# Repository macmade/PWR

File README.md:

PWR
===

About
-----

+5 volt power supply for breadboards using a 12 volt DC wall adapter or a 9 volt battery.

### Software

Schemas and PCB layouts are created with KiCad:  
http://www.kicad-pcb.org

#### Footprints Library

This project requires the [XS-Labs KiCad Library](https://github.com/macmade/XS-KiCad-Library) to be installed in KiCad.

### Board

Here's what the board looks like:

Bill Of Materials
-----------------

| Manufacturer            | Part No.             | Details                                                                  | Quantity |
|-------------------------|----------------------|--------------------------------------------------------------------------|----------|
| CUI Devices             | [PJ-102AH]           | DC Power Jack                                                            | 1        |
| Keystone Electronics    | [1291]               | 9V Battery Snap Holder                                                   | 1        |
| ON Semiconductor        | [1N4001G]            | Rectifier 50V 1A Standard                                                | 2        |
| Texas Instruments       | [LM7805CT/NOPB]      | Linear Voltage Regulator 5V                                              | 1        |
| Vishay                  | [MAL214250101E3]     | Aluminium Electrolytic Capacitor - Radial Leaded 100uF 35V 20%           | 1        |
| Vishay                  | [MAL214258109E3]     | Aluminium Electrolytic Capacitor - Radial Leaded 10uF 63V 20%            | 1        |
| Murata                  | [RCER71H334K1K1H03B] | Multilayer Ceramic Capacitor - Radial Leaded 0.33uF 50V 10%              | 1        |
| Murata                  | [RCER71H104K0K1H03B] | Multilayer Ceramic Capacitor - Radial Leaded 0.1uF 50V 10%               | 1        |
| VCC                     | [4302H1-12V]         | Standard LEDs - Red - 12V                                                | 1        |
| VCC                     | [4302H3-12V]         | Standard LEDs - Amber - 12V                                              | 1        |
| VCC                     | [4302H5-12V]         | Standard LEDs - Green - 12V                                              | 1        |
| Vishay                  | [CCF071K00JKE36]     | Metal Film Resistor - Through Hole 1/4watt 1Kohms 5%                     | 1        |
| Vishay                  | [CCF07390RJKE36]     | Metal Film Resistor - Through Hole 1/4watt 390ohms 5%                    | 2        |
| NKK Switches            | [M2012SA1W03]        | Toggle Switch ON-ON PC SPDT                                              | 1        |
| Wurth Elektronik        | [691214110002]       | Fixed Terminal Block WR-TBL 300VAC 10A 2P Horizontal                     | 1        |

[PJ-102AH]: https://www.mouser.ch/ProductDetail/490-PJ-102AH
[1291]: https://www.mouser.ch/ProductDetail/534-1291
[1N4001G]: https://www.mouser.ch/ProductDetail/863-1N4001G
[LM7805CT/NOPB]: https://www.mouser.ch/ProductDetail/926-LM7805CT-NOPB
[MAL214250101E3]: https://www.mouser.ch/ProductDetail/594-MAL214250101E3
[MAL214258109E3]: https://www.mouser.ch/ProductDetail/594-MAL214258109E3
[RCER71H334K1K1H03B]: https://www.mouser.ch/ProductDetail/81-RCER71H334K1K1H3B
[RCER71H104K0K1H03B]: https://www.mouser.ch/ProductDetail/81-RCER71H104K0K1H3B
[4302H1-12V]: https://www.mouser.ch/ProductDetail/606-4302H1-12V
[4302H3-12V]: https://www.mouser.ch/ProductDetail/606-4302H3-12V
[4302H5-12V]: https://www.mouser.ch/ProductDetail/606-4302H5-12V
[CCF071K00JKE36]: https://www.mouser.ch/ProductDetail/71-CCF071K00JKE36
[CCF07390RJKE36]: https://www.mouser.ch/ProductDetail/71-CCF07390RJKE36
[M2012SA1W03]: https://www.mouser.ch/ProductDetail/633-M2012A03
[691214110002]: https://www.mouser.ch/ProductDetail/710-691214110002

License
-------

All project files are released under the terms of the CERN Open Hardware License - CERN OHL v.1.2.

Repository Infos
----------------

    Owner:          Jean-David Gadina - XS-Labs
    Web:            www.xs-labs.com
    Blog:           www.noxeos.com
    Twitter:        @macmade
    GitHub:         github.com/macmade
    LinkedIn:       ch.linkedin.com/in/macmade/
    StackOverflow:  stackoverflow.com/users/182676/macmade

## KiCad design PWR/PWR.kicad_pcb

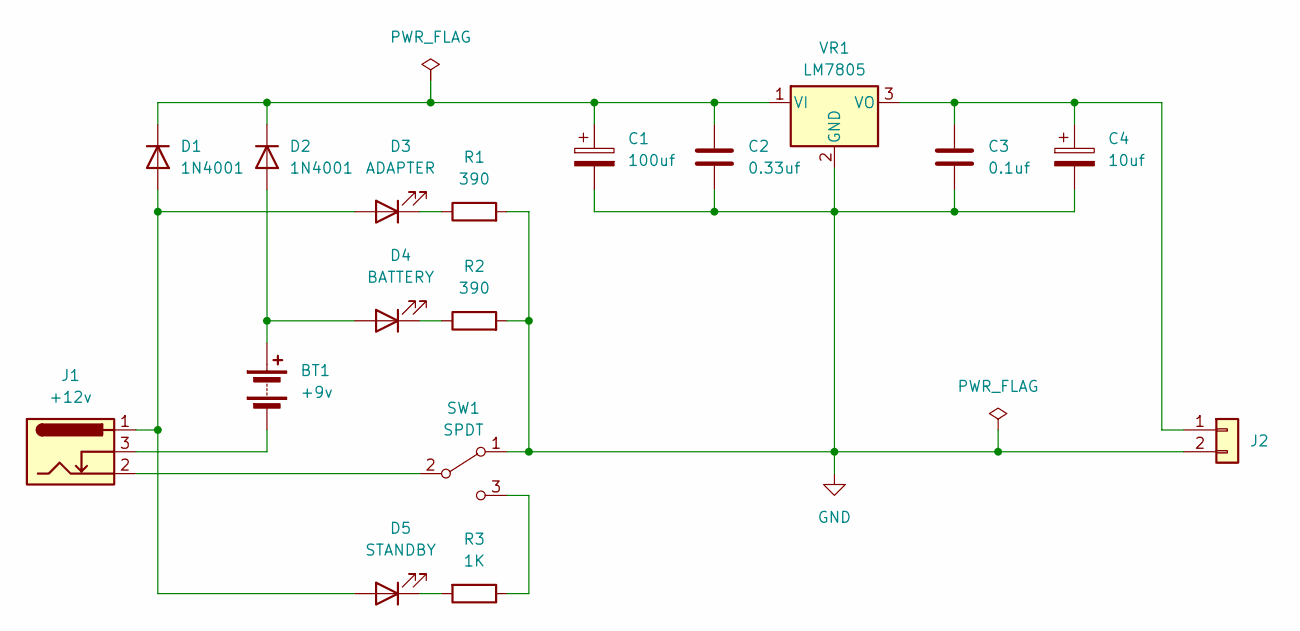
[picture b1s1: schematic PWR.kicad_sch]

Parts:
BT1: +9v; Battery-Keystone-1291-9v-Holder
C1: 100uf; Capacitor-Vishay-142-RHS-6.3x11x2.5mm
C2: 0.33uf; Capacitor-Murata-RCE-K-5mm.step
C3: 0.1uf; Capacitor-Murata-RCE-K-5mm.step
C4: 10uf; Capacitor-Vishay-142-RHS-5x11x2mm
D1, D2: 1N4001; Diode-DO-41
D3: ADAPTER; LED-T1-34-5mm-tabs
D4: BATTERY; LED-T1-34-5mm-tabs
D5: STANDBY; LED-T1-34-5mm-tabs
J1: +12v; Plug-DC-Barrel-Jack-2.1mm-CUI-PJ-102AH
J2: Connector-Wurth-Terminal-Block-2P-3.5mm-691214110002
R1, R2: 390; Resistor-Vishay-CCF07
R3: 1K; Resistor-Vishay-CCF07
SW1: SPDT; Switch-SPDT-NKK-Series-M
VR1: LM7805; Regulator-Failrchild-LM78XX-TO-220

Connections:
GND: C1.2, C2.2, C3.2, C4.2, J2.2, R1.2, R2.2, SW1.1 (A), VR1.2 (GND)
unnamed: BT1.1 (+), D2.2 (A), D4.2 (A)
unnamed: BT1.2 (-), J1.3
unnamed: D1.2 (A), D3.2 (A), D5.2 (A), J1.1
unnamed: C1.1, C2.1, D1.1 (K), D2.1 (K), VR1.1 (VI)
unnamed: D3.1 (K), R1.1
unnamed: D4.1 (K), R2.1
unnamed: D5.1 (K), R3.2
unnamed: C3.1, C4.1, J2.1, VR1.3 (VO)
unnamed: J1.2, SW1.2 (B)
unnamed: R3.1, SW1.3 (C)

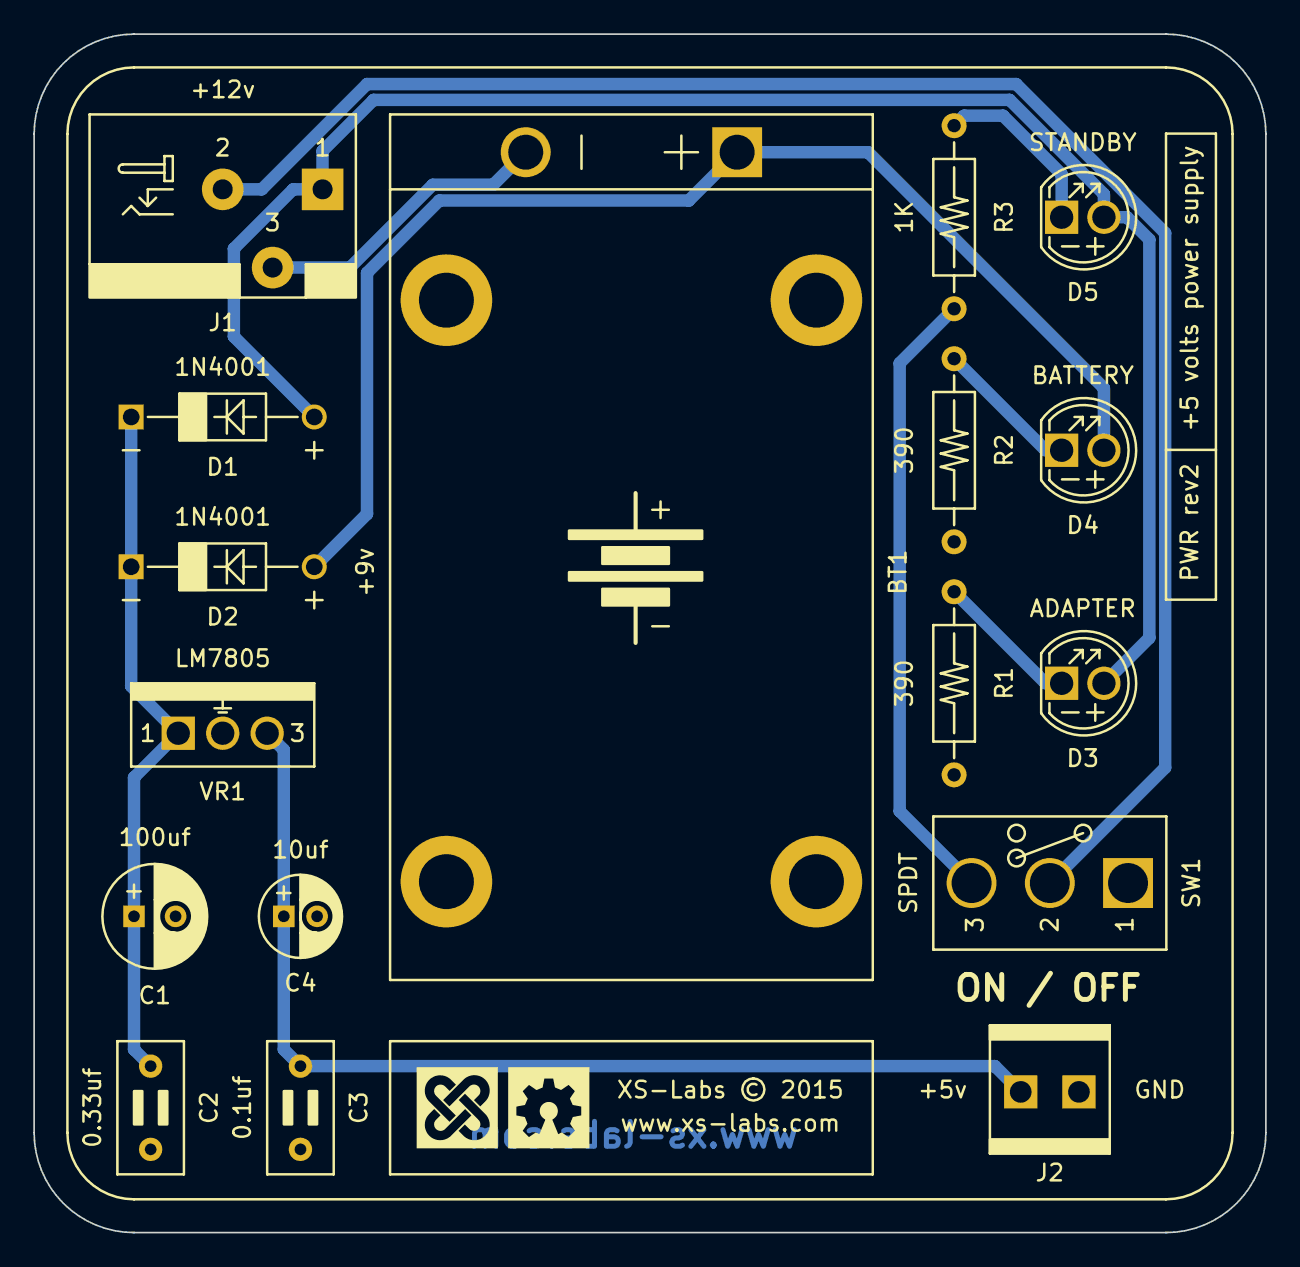
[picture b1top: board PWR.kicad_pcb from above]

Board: 2 copper layers, 74.0 x 72.0 mm, 17 parts (0 on the bottom side), 11 nets.

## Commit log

2015-10-09 Initial setup...
2015-10-09 README + LICENSE
2015-10-09 Initial KiCad project import.
2015-10-09 Added the base schamatic...
2015-10-10 Added headers and power flags.
2015-10-10 Fixed capacitor values.
2015-10-10 Footprints...
2015-10-10 Netlist...
2015-10-11 Cleanup. Added extra capacitors.
2015-10-11 Cleanup...
2015-10-11 Added the XS footprint library as a submodule.
2015-10-11 XS.pretty
2015-10-13 Submodules...
2015-10-13 Netlist + footprints
2015-10-13 Submodules..:
2015-10-15 PCB layout...
2015-10-15 PCB edges.
2015-10-15 Track width & clearance.
2015-10-15 Routing...
2015-10-15 Fixed pad numbers on Adafruit DC barrel jack.
2015-10-15 Inverted logo...
2015-10-15 Copper pour.
2015-10-15 Gerber files.
2015-10-16 README: board preview.
2015-10-16 BOM...
2015-10-17 Added AC plug mix.
2015-10-17 PCB: starting over...
2015-10-17 PCB - Placement.
2015-10-20 Better routing.
2015-10-28 XS.lib
2015-10-29 Now using XS library for schematic.
2015-10-29 Fixed polarized capacitor pads.
2015-10-29 Fixed battery pads.
2017-01-11 README
2023-10-06 chore: XS.pretty update
2023-10-06 chore: GitHub sponsors
2023-10-06 chore: COC
2023-10-06 chore: README
2023-10-24 chore: Removing Gerber files
2023-10-24 chore: Removing backup files
2023-10-24 chore: README update
2023-10-24 chore: Removed XS.pretty
2023-10-27 chore: Starting from scratch with KiCad 7
2023-10-27 chore: README+Renders
2023-10-27 chore: Renders
2023-10-27 feat: Added the KiCad project
2023-10-28 feat: Replaced the pin header by a terminal block. Changed the LEDs labels.
2023-10-28 chore: BOM update
2023-10-28 chore: Assets update
2023-10-30 chore: Footprints update
2023-11-01 fix: DRC fixes
2023-11-02 fix: Changed standby LED to 1K
2023-11-02 style: PCB update
2023-11-03 chore: Cleanup
2023-11-03 chore: BOM + Assets update
2023-11-03 chore: Using D for LEDs instead of DS
2023-11-15 chore: Updated footprints and PCB

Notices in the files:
PWR/PWR.kicad_pcb:
XS-Labs © 2015
README.md:
License: ohl
